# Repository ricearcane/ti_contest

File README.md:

ti_contest
==========

Files for the 2014 TI Analog Design Competition

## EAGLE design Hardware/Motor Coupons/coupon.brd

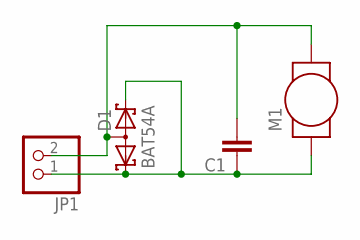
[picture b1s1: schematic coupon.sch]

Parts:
C1: C-EUC0805; C0805
D1: BAT54A; SOT23
JP1: PINHD-1X2; 1X02
M1: PAGER-PANCAKE; PANCAKE

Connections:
GND: C1.1, D1.1 (K1), D1.2 (K2), JP1.1, M1.P$1
unnamed: C1.2, D1.3 (AA), JP1.2, M1.P$2

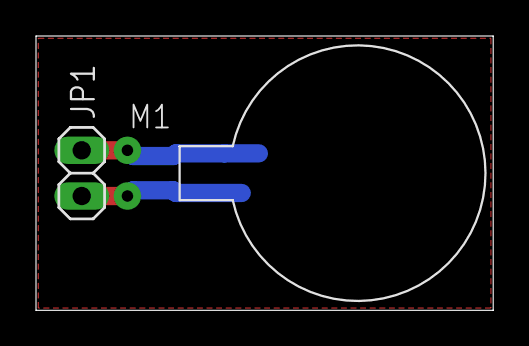
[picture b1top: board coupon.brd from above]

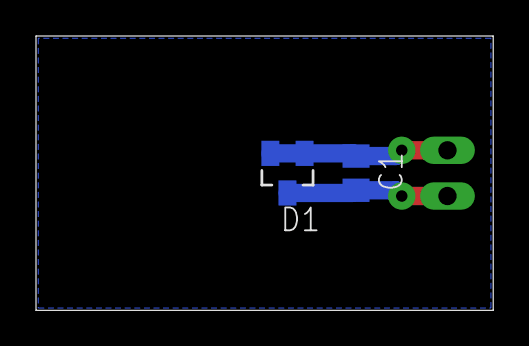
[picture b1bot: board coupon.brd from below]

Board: 2 copper layers, 25.4 x 15.2 mm, 4 parts (2 on the bottom side), 2 nets.

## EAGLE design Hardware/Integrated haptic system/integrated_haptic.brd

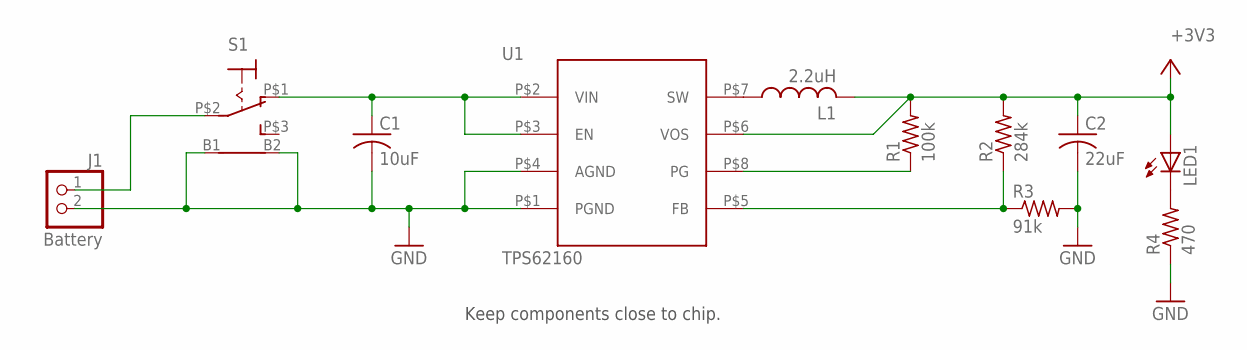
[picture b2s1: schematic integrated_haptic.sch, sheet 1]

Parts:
C1: 10uF; C1206K
C2: 22uF; C1206K
J1: Battery; 1X02
L1: 2.2uH; L2520P
LED1: LEDCHIP-LED0805; CHIP-LED0805
R1: 100k; R0603
R2: 284k; R0603
R3: 91k; R0603
R4: 470; R0603
S1: 7101MD9AQE; 7101MD9A
U1: TPS62160; VSSOP

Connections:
+3V3: C2.1, L1.2, LED1.A, R1.2, R2.2, U1.P$6 (VOS); also elsewhere on the board
GND: C1.2, C2.2, J1.2, R3.2, R4.1, S1.B1 (B), S1.B2 (B1), U1.P$1 (PGND), U1.P$4 (AGND); also elsewhere on the board
unnamed: L1.1, U1.P$7 (SW)
unnamed: J1.1, S1.P$2
unnamed: LED1.C, R4.2
unnamed: R2.1, R3.1, U1.P$5 (FB)
POWER_PG: R1.1, U1.P$8 (PG)
VBAT: C1.1, S1.P$1 (O), U1.P$2 (VIN), U1.P$3 (EN)

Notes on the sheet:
Keep components close to chip.

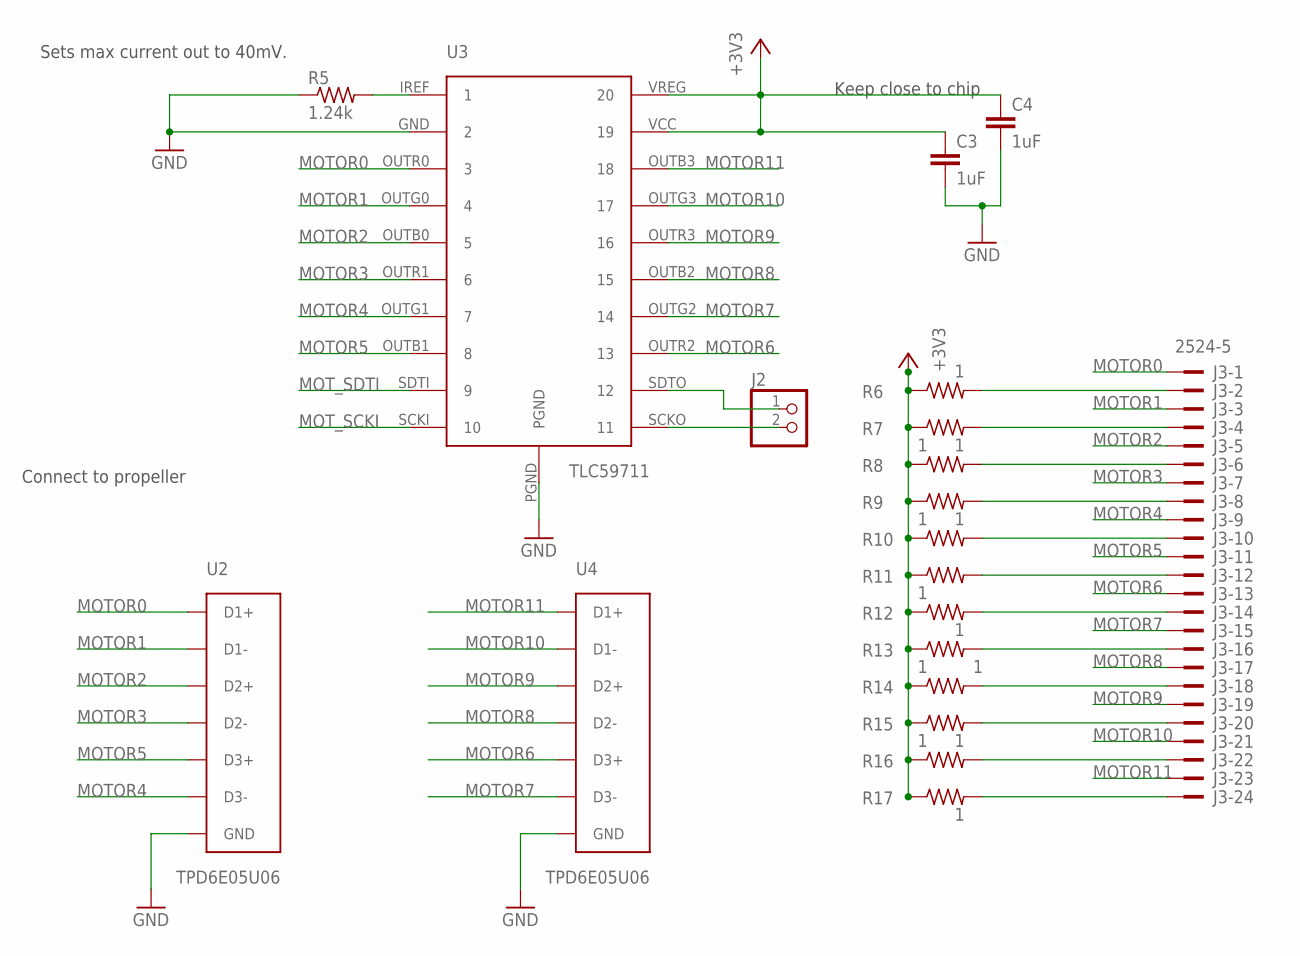
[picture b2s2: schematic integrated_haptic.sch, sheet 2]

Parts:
C3, C4: 1uF; C0805K
J2: PINHD-1X2; 1X02
J3: 2524-5; PAK100/2500-5-24
R5: 1.24k; R0603
R6, R7, R8, R9, R10, R11, R12, R13, R14, R15, R16, R17: 1; R0805
U2, U4: TPD6E05U06; PUQFN-N14
U3: TLC59711

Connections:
+3V3: C3.1, C4.1, R6.1, R7.1, R8.1, R9.1, R10.1, R11.1, R12.1, R13.1, R14.1, R15.1, R16.1, R17.1, U3.VCC (19), U3.VREG (20); also elsewhere on the board
GND: C3.2, C4.2, R5.1, U2.P$5 (GND), U2.P$10 (GND), U3.GND (2), U3.PGND, U4.P$5 (GND), U4.P$10 (GND); also elsewhere on the board
MOTOR0: J3.1, U2.P$1 (D1+), U2.P$14 (D1+), U3.OUTR0 (3)
MOTOR1: J3.3, U2.P$2 (D1-), U2.P$13 (D1-), U3.OUTG0 (4)
MOTOR2: J3.5, U2.P$3 (D2+), U2.P$12 (D2+), U3.OUTB0 (5)
MOTOR3: J3.7, U2.P$4 (D2-), U2.P$11 (D2-), U3.OUTR1 (6)
MOTOR4: J3.9, U2.P$6 (D3-), U2.P$9 (D3-), U3.OUTG1 (7)
MOTOR5: J3.11, U2.P$7 (D3+), U2.P$8 (D3+), U3.OUTB1 (8)
MOTOR6: J3.13, U3.OUTR2 (13), U4.P$7 (D3+), U4.P$8 (D3+)
MOTOR7: J3.15, U3.OUTG2 (14), U4.P$6 (D3-), U4.P$9 (D3-)
MOTOR8: J3.17, U3.OUTB2 (15), U4.P$4 (D2-), U4.P$11 (D2-)
MOTOR9: J3.19, U3.OUTR3 (16), U4.P$3 (D2+), U4.P$12 (D2+)
MOTOR10: J3.21, U3.OUTG3 (17), U4.P$2 (D1-), U4.P$13 (D1-)
MOTOR11: J3.23, U3.OUTB3 (18), U4.P$1 (D1+), U4.P$14 (D1+)
MOT_SCKI: U3.SCKI (10); also elsewhere on the board
MOT_SDTI: U3.SDTI (9); also elsewhere on the board
unnamed: R5.2, U3.IREF (1)
unnamed: J3.24, R17.2
unnamed: J3.22, R16.2
unnamed: J3.20, R15.2
unnamed: J3.18, R14.2
unnamed: J3.16, R13.2
unnamed: J3.14, R12.2
unnamed: J3.12, R11.2
unnamed: J3.10, R10.2
unnamed: J3.8, R9.2
unnamed: J3.6, R8.2
unnamed: J3.4, R7.2
unnamed: J3.2, R6.2
unnamed: J2.2, U3.SCKO (11)
unnamed: J2.1, U3.SDTO (12)

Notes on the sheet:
Sets max current out to 40mV.
Keep close to chip
Connect to propeller

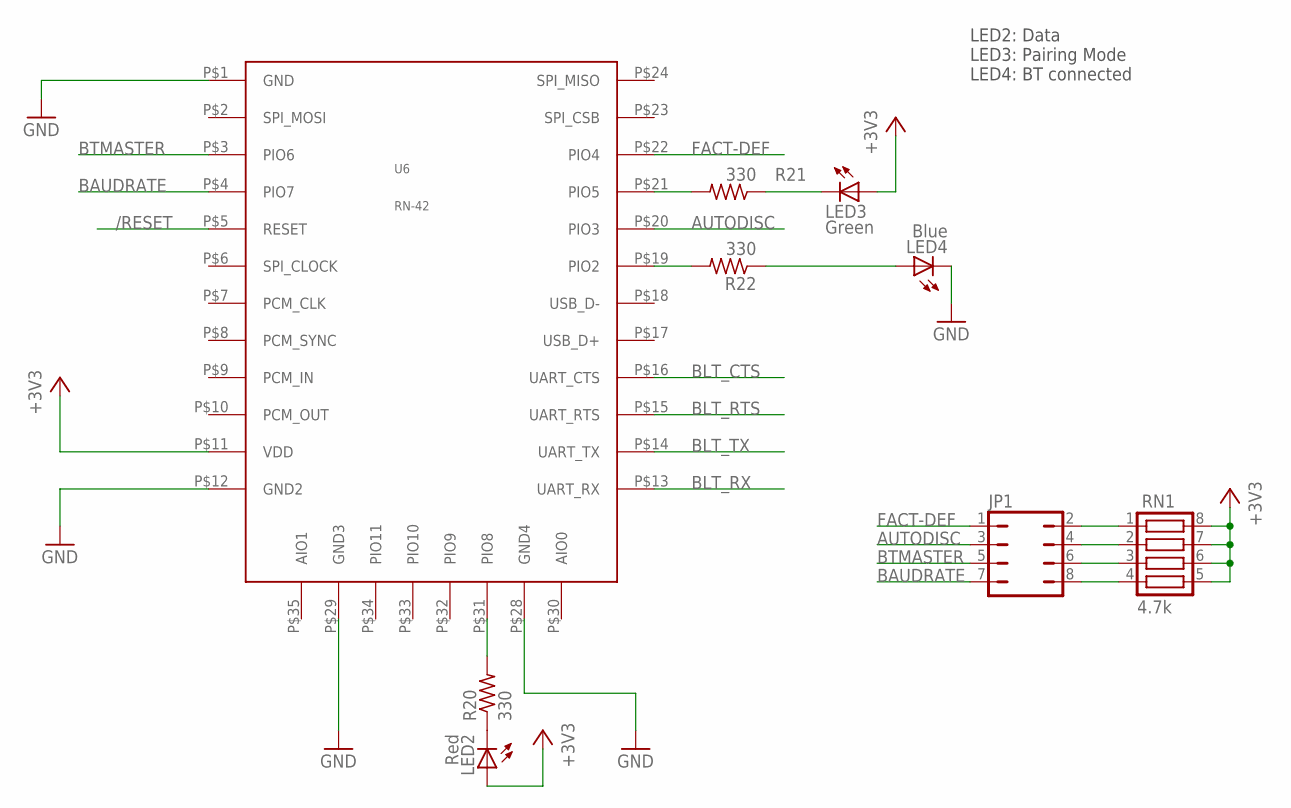
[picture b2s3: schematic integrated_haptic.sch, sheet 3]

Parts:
JP1: JP4Q
LED2: Red; CHIP-LED0805
LED3: Green; CHIP-LED0805
LED4: Blue; CHIP-LED0805
R20, R21, R22: 330; R0603
RN1: 4.7k; CTS742C083
U6: RN-42

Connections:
+3V3: LED2.A, LED3.A, RN1.5, RN1.6, RN1.7, RN1.8, U6.P$11 (VDD); also elsewhere on the board
/RESET: U6.P$5 (RESET); also elsewhere on the board
AUTODISC: JP1.3, U6.P$20 (PIO3)
BAUDRATE: JP1.7, U6.P$4 (PIO7)
BLT_CTS: U6.P$16 (UART_CTS); also elsewhere on the board
BLT_RTS: U6.P$15 (UART_RTS); also elsewhere on the board
BLT_RX: U6.P$13 (UART_RX); also elsewhere on the board
BLT_TX: U6.P$14 (UART_TX); also elsewhere on the board
BTMASTER: JP1.5, U6.P$3 (PIO6)
FACT-DEF: JP1.1, U6.P$22 (PIO4)
GND: LED4.C, U6.P$1 (GND), U6.P$12 (GND2), U6.P$28 (GND4), U6.P$29 (GND3); also elsewhere on the board
unnamed: LED2.C, R20.1
unnamed: R21.2, U6.P$21 (PIO5)
unnamed: LED3.C, R21.1
unnamed: R22.2, U6.P$19 (PIO2)
unnamed: LED4.A, R22.1
unnamed: R20.2, U6.P$31 (PIO8)
unnamed: JP1.8, RN1.4
unnamed: JP1.6, RN1.3
unnamed: JP1.4, RN1.2
unnamed: JP1.2, RN1.1

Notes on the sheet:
LED2: Data LED3: Pairing Mode LED4: BT connected

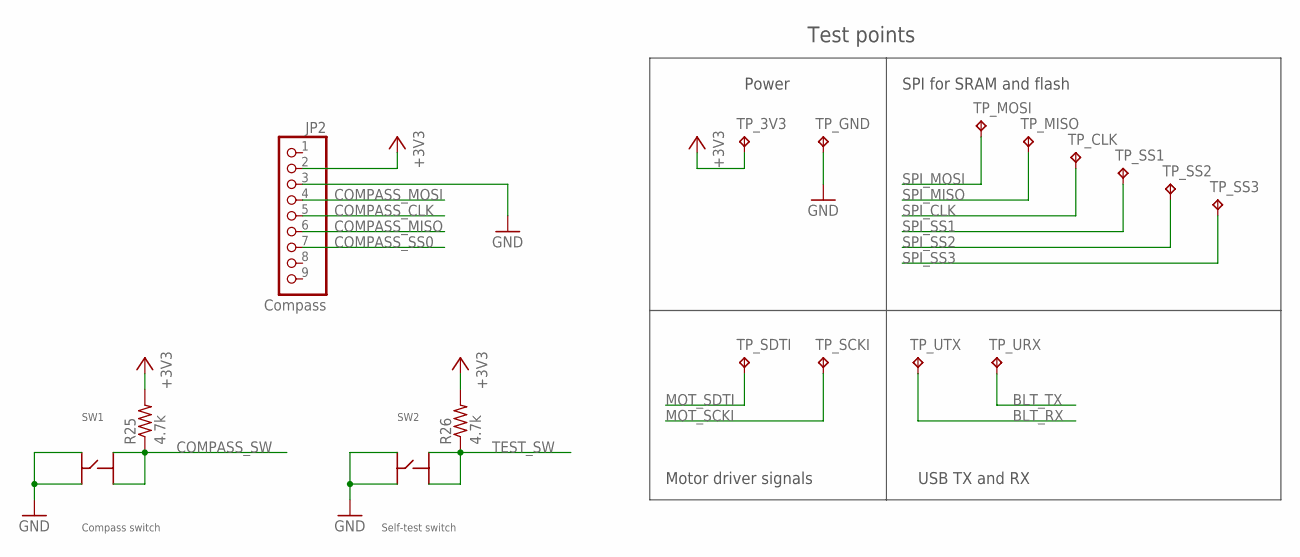
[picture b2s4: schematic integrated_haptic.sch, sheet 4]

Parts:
JP2: Compass; 1X09
R25, R26: 4.7k; R0603
SW1: Compass switch; 6MMX6MM
SW2: Self-test switch; 6MMX6MM
TP_3V3: TPPAD1-13; P1-13
TP_CLK: TPPAD1-13; P1-13
TP_GND: TPPAD1-13; P1-13
TP_MISO: TPPAD1-13; P1-13
TP_MOSI: SPI_MOSI; P1-13
TP_SCKI: TPPAD1-13; P1-13
TP_SDTI: TPPAD1-13; P1-13
TP_SS1, TP_SS2, TP_SS3: TPPAD1-13; P1-13
TP_URX: TPPAD1-13; P1-13
TP_UTX: TPPAD1-13; P1-13

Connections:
+3V3: JP2.2, R25.2, R26.2, TP_3V3.TP; also elsewhere on the board
BLT_RX: TP_UTX.TP; also elsewhere on the board
BLT_TX: TP_URX.TP; also elsewhere on the board
COMPASS_CLK: JP2.5; also elsewhere on the board
COMPASS_MISO: JP2.6; also elsewhere on the board
COMPASS_MOSI: JP2.4; also elsewhere on the board
COMPASS_SS0: JP2.7; also elsewhere on the board
COMPASS_SW: R25.1, SW1.P$2, SW1.P$4; also elsewhere on the board
GND: JP2.3, SW1.P$1, SW1.P$3, SW2.P$1, SW2.P$3, TP_GND.TP; also elsewhere on the board
MOT_SCKI: TP_SCKI.TP; also elsewhere on the board
MOT_SDTI: TP_SDTI.TP; also elsewhere on the board
SPI_CLK: TP_CLK.TP; also elsewhere on the board
SPI_MISO: TP_MISO.TP; also elsewhere on the board
SPI_MOSI: TP_MOSI.TP; also elsewhere on the board
SPI_SS1: TP_SS1.TP; also elsewhere on the board
SPI_SS2: TP_SS2.TP; also elsewhere on the board
SPI_SS3: TP_SS3.TP; also elsewhere on the board
TEST_SW: R26.1, SW2.P$2, SW2.P$4; also elsewhere on the board

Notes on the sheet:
Power
SPI for SRAM and flash
Motor driver signals
USB TX and RX
Test points

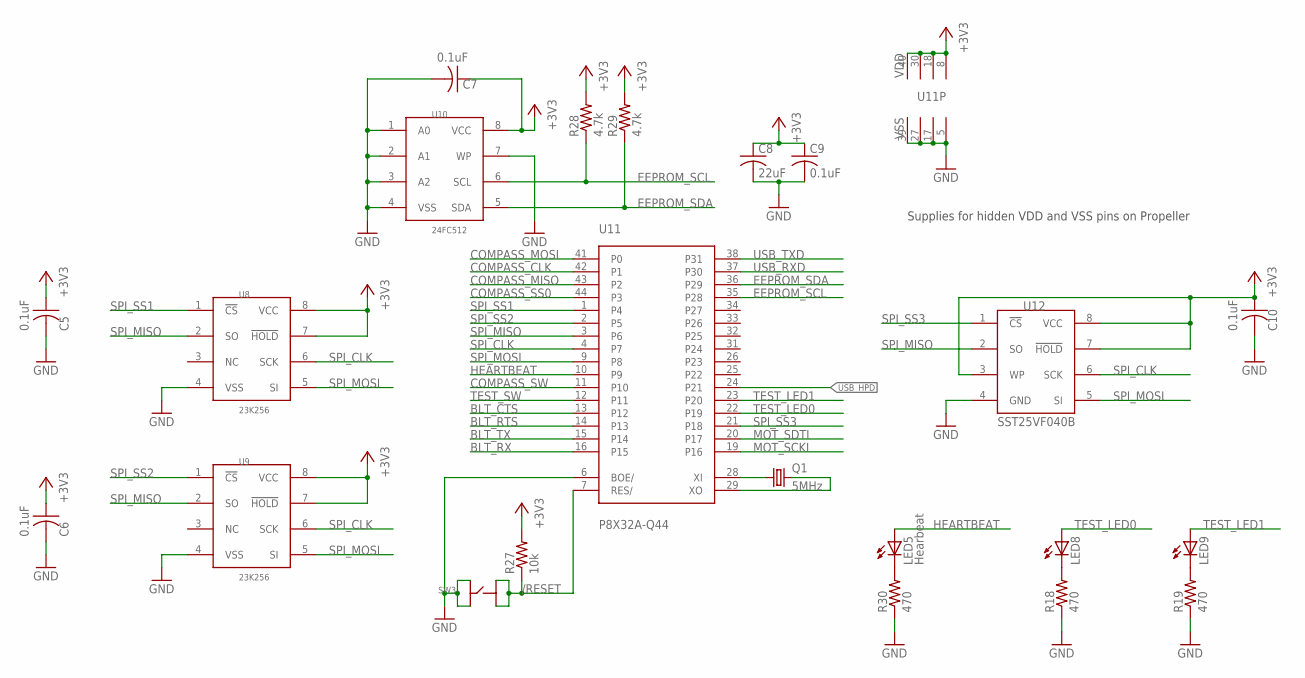
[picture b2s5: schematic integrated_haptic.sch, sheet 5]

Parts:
C5, C6, C7, C9, C10: 0.1uF; C0805K
C8: 22uF; C1206K
LED5: Hearbeat; CHIP-LED0805
LED8, LED9: LEDCHIP-LED0805; CHIP-LED0805
Q1: 5MHz; HC49UP
R18, R19, R30: 470; R0603
R27: 10k; R0603
R28, R29: 4.7k; R0603
SW3: PUSHBUTTON; 6MMX6MM
U8, U9: 23K256; SOIC8
U10: 24FC512; SOIC8
U11: P8X32A-Q44
U12: SST25VF040B; SOIC8

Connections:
+3V3: C5.1, C6.1, C7.1, C8.1, C9.1, C10.1, R27.2, R28.2, R29.2, U8.7 (!HOLD), U8.8 (VCC), U9.7 (!HOLD), U9.8 (VCC), U10.8 (VCC), U11.8 (VDD), U11.18 (VDD), U11.30 (VDD), U11.40 (VDD), U12.3 (WP), U12.7 (!HOLD), U12.8 (VCC); also elsewhere on the board
/RESET: R27.1, SW3.P$2, SW3.P$4, U11.7 (RES/); also elsewhere on the board
BLT_CTS: U11.13 (P12); also elsewhere on the board
BLT_RTS: U11.14 (P13); also elsewhere on the board
BLT_RX: U11.16 (P15); also elsewhere on the board
BLT_TX: U11.15 (P14); also elsewhere on the board
COMPASS_CLK: U11.42 (P1); also elsewhere on the board
COMPASS_MISO: U11.43 (P2); also elsewhere on the board
COMPASS_MOSI: U11.41 (P0); also elsewhere on the board
COMPASS_SS0: U11.44 (P3); also elsewhere on the board
COMPASS_SW: U11.11 (P10); also elsewhere on the board
EEPROM_SCL: R28.1, U10.6 (SCL), U11.35 (P28)
EEPROM_SDA: R29.1, U10.5 (SDA), U11.36 (P29)
GND: C5.2, C6.2, C7.2, C8.2, C9.2, C10.2, R18.1, R19.1, R30.1, SW3.P$1, SW3.P$3, U8.4 (VSS), U9.4 (VSS), U10.1 (A0), U10.2 (A1), U10.3 (A2), U10.4 (VSS), U10.7 (WP), U11.5 (VSS), U11.6 (BOE/), U11.17 (VSS), U11.27 (VSS), U11.39 (VSS), U12.4 (GND); also elsewhere on the board
HEARTBEAT: LED5.A, U11.10 (P9)
MOT_SCKI: U11.19 (P16); also elsewhere on the board
MOT_SDTI: U11.20 (P17); also elsewhere on the board
unnamed: LED8.C, R18.2
unnamed: LED5.C, R30.2
unnamed: LED9.C, R19.2
SPI_CLK: U8.6 (SCK), U9.6 (SCK), U11.4 (P7), U12.6 (SCK); also elsewhere on the board
SPI_MISO: U8.2 (SO), U9.2 (SO), U11.3 (P6), U12.2 (SO); also elsewhere on the board
SPI_MOSI: U8.5 (SI), U9.5 (SI), U11.9 (P8), U12.5 (SI); also elsewhere on the board
SPI_SS1: U8.1 (!CS), U11.1 (P4); also elsewhere on the board
SPI_SS2: U9.1 (!CS), U11.2 (P5); also elsewhere on the board
SPI_SS3: U11.21 (P18), U12.1 (!CS); also elsewhere on the board
TEST_LED0: LED8.A, U11.22 (P19)
TEST_LED1: LED9.A, U11.23 (P20)
TEST_SW: U11.12 (P11); also elsewhere on the board
USB_HPD: U11.24 (P21); also elsewhere on the board
USB_RXD: U11.37 (P30); also elsewhere on the board
USB_TXD: U11.38 (P31); also elsewhere on the board
XTAL0: Q1.2, U11.29 (XO)
XTAL1: Q1.1, U11.28 (XI)

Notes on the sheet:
Supplies for hidden VDD and VSS pins on Propeller

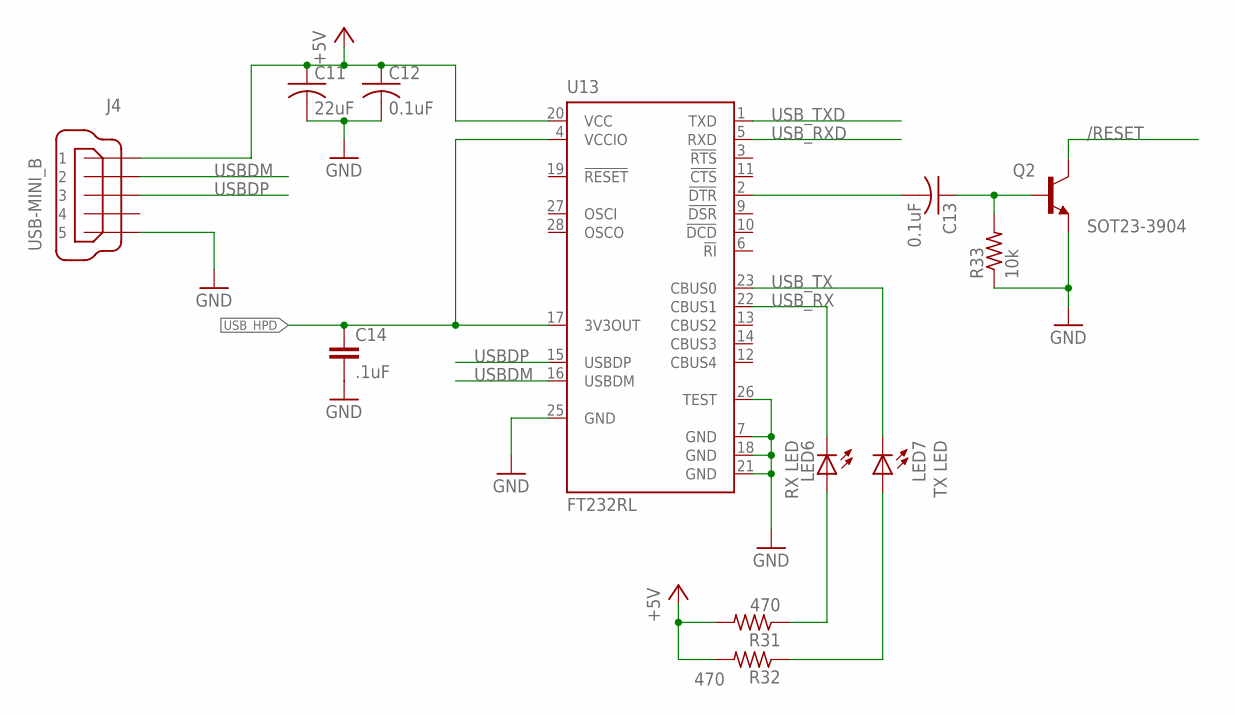
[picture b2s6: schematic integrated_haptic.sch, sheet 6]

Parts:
C11: 22uF; C1206K
C12, C13: 0.1uF; C0805K
C14: .1uF; C0805
J4: USB-MINI_B; USB_MINI_B
LED6: RX LED; CHIP-LED0805
LED7: TX LED; CHIP-LED0805
Q2: SOT23-3904; SOT23-BEC
R31, R32: 470; R0603
R33: 10k; R0603
U13: FT232RL; SSOP28

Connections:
+5V: C11.1, C12.1, J4.1, R31.2, R32.2, U13.20 (VCC)
/RESET: Q2.C; also elsewhere on the board
GND: C11.2, C12.2, C14.2, J4.5, Q2.E, R33.1, U13.7 (GND), U13.18 (GND), U13.21 (GND), U13.25 (GND), U13.26 (TEST); also elsewhere on the board
unnamed: C13.2, U13.2 (!DTR)
unnamed: LED6.A, R31.1
unnamed: LED7.A, R32.1
unnamed: C13.1, Q2.B, R33.2
USBDM: J4.2, U13.16 (USBDM)
USBDP: J4.3, U13.15 (USBDP)
USB_HPD: C14.1, U13.4 (VCCIO), U13.17 (3V3OUT); also elsewhere on the board
USB_RX: LED6.C, U13.22 (CBUS1)
USB_RXD: U13.5 (RXD); also elsewhere on the board
USB_TX: LED7.C, U13.23 (CBUS0)
USB_TXD: U13.1 (TXD); also elsewhere on the board

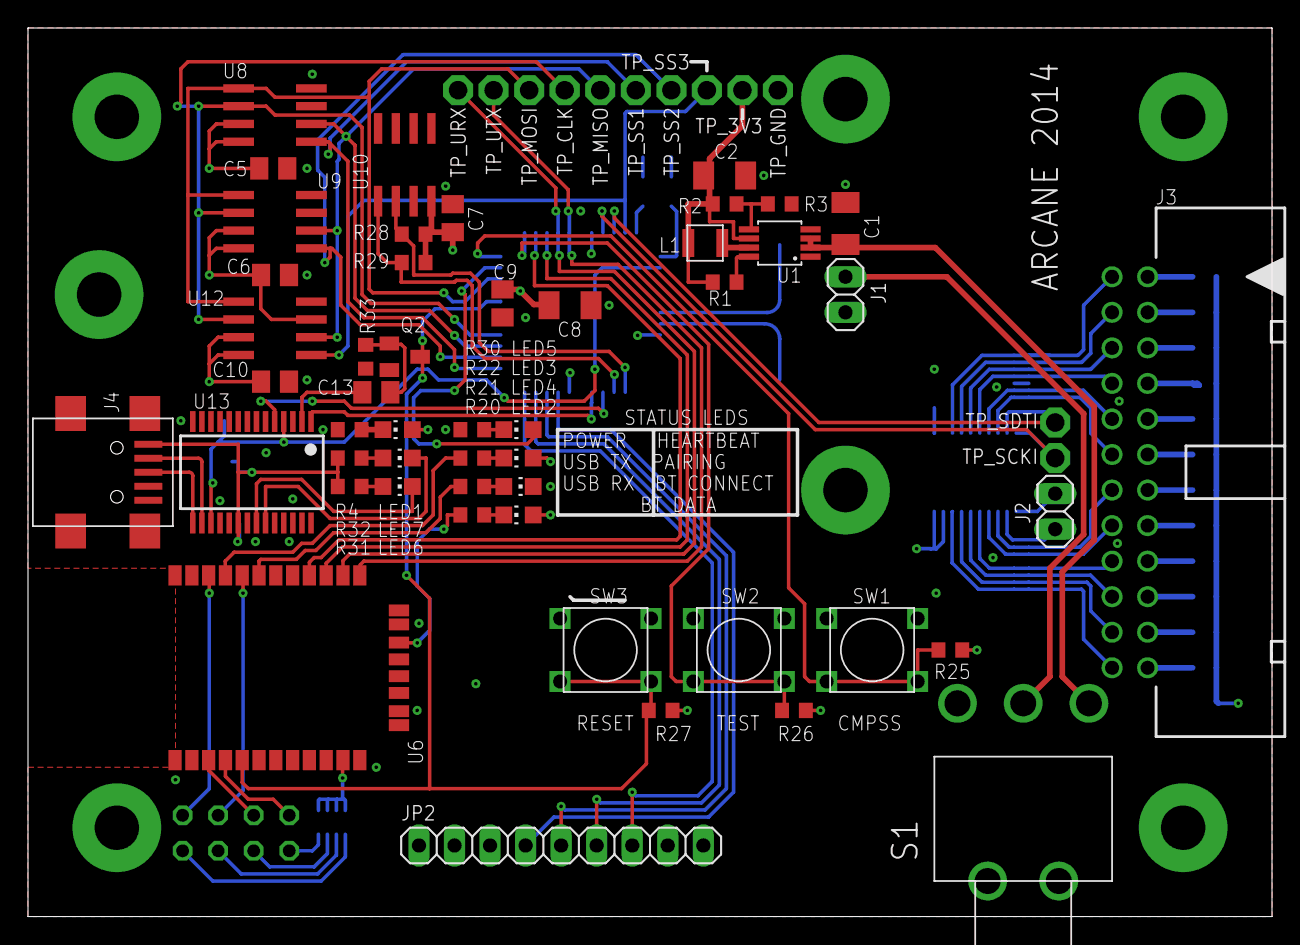
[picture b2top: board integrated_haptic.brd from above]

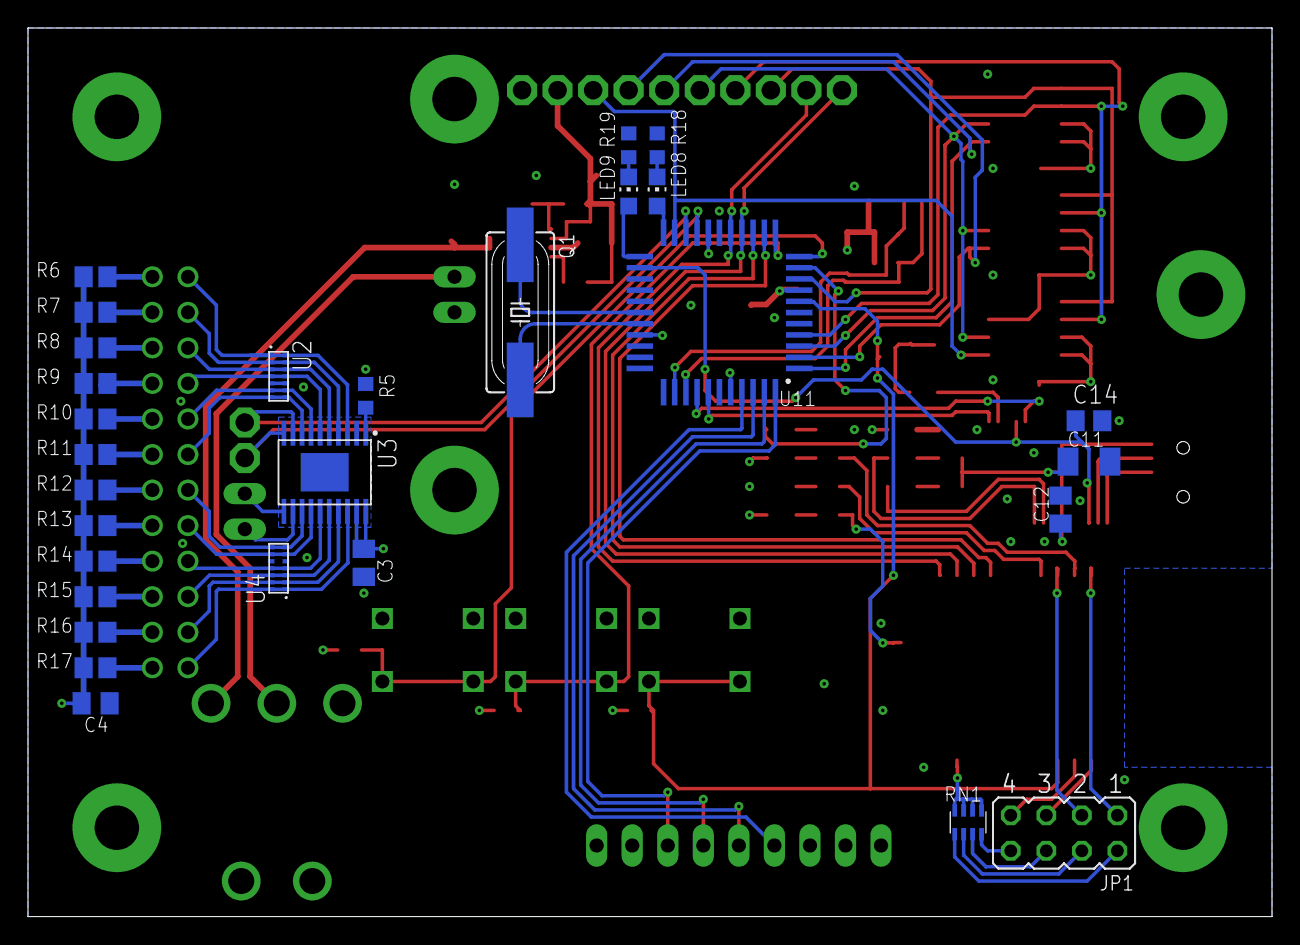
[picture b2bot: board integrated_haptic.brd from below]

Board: 4 copper layers, 88.9 x 63.5 mm, 91 parts (29 on the bottom side), 90 nets.

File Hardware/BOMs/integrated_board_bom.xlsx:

Value | Device | Package | Parts | Description | Qty | Digikey Part Number | Customer Reference | Notes
1 | R-US_R0805 | R0805 | R6, R7, R8, R9, R10, R11, R12, R13, R14, R15, R16, R17 | RESISTOR, American symbol | 12 | RMCF0805JT1R00CT-ND | R6, R7, R8, R9, R10, R11, R12, R13, R14, R15, R16, R17
330 | R-US_R0603 | R0603 | R20, R21, R22 | RESISTOR, American symbol | 3 | 1276-5050-1-ND | R20, R21, R22
470 | R-US_R0603 | R0603 | R4, R18, R19, R30, R31, R32 | RESISTOR, American symbol | 6 | 311-470GRCT-ND | R4, R18, R19, R30, R31, R32
1.24k | R-US_R0603 | R0603 | R5 | RESISTOR, American symbol | 1 | P1.24KHCT-ND | R5
4.7k | R-US_R0603 | R0603 | R25, R26, R28, R29 | RESISTOR, American symbol | 4 | 311-4.7KGRCT-ND | R25, R26, R28, R29
10k | R-US_R0603 | R0603 | R27, R33 | RESISTOR, American symbol | 2 | 311-10KGRCT-ND | R27, R33
91k | R-US_R0603 | R0603 | R3 | RESISTOR, American symbol | 1 | 311-91.0KHRCT-ND | R3
100k | R-US_R0603 | R0603 | R1 | RESISTOR, American symbol | 1 | 311-100KGRCT-ND | R1
284k | R-US_R0603 | R0603 | R2 | RESISTOR, American symbol | 1 | RR08P284KDCT-ND | R2
4.7k | CTS742C083 | CTS742C083 | RN1 | Chip Resistor Array 4 Single Resistor | 1 | TC164J-4.7KCT-ND | RN1
0.1uF | C-USC0805K | C0805K | C5, C6, C7, C9, C10, C12, C13 | CAPACITOR, American symbol | 7 | 311-1361-1-ND | C5, C6, C7, C9, C10, C12, C13
1uF | C-EUC0805K | C0805K | C3, C4 | CAPACITOR, European symbol | 2 | 1276-1029-1-ND | C3, C4
10uF | C-USC1206K | C1206K | C1 | CAPACITOR, American symbol | 1 | 587-1353-1-ND | C1
22uF | C-USC1206K | C1206K | C2, C8, C11 | CAPACITOR, American symbol | 3 | 1276-3048-1-ND | C2, C8, C11
2.2uH | L-USL2520P | L2520P | L1 | INDUCTOR, American symbol | 1 | 445-3670-1-ND | L1
Amber | LEDCHIP-LED0805 | CHIP-LED0805 | LED8 | LED | 1 | 516-1431-1-ND | LED8
Blue | LEDCHIP-LED0805 | CHIP-LED0805 | LED4 | LED | 1 | 160-1645-1-ND | LED4
Green | LEDCHIP-LED0805 | CHIP-LED0805 | LED3,LED7 | LED | 2 | 160-1423-1-ND | LED3,LED7
Red | LEDCHIP-LED0805 | CHIP-LED0805 | LED1, LED2, LED6, LED9 | LED | 4 | 160-1415-1-ND | LED1, LED2, LED6, LED9
White | LEDCHIP-LED0805 | CHIP-LED0805 | LED5 | LED | 1 | 160-1738-1-ND | LED5
23K256 | 23K256 | SOIC8 | U8, U9 |  | 2 | 23K256-I/SN-ND | U8, U9
24FC512 | 24FC512 | SOIC8 | U10 |  | 1 | 24FC512-I/SN-ND | U10
FT232RL | FT232RL | SSOP28 | U13 |  | 1 | 768-1007-1-ND | U13
P8X32A-Q44 | Propeller | P8X32A-Q44 | U11 |  | 1 | P8X32A-Q44-ND | U11
RN-42 | Bluetooth Module | RN-42 | U6 |  | 1 | 740-1038-ND | U6
SST25VF040B | SST25VF040B | SOIC8 | U12 |  | 1 | 804-25VF040B5CSAF | U12 | MOUSER PART
TLC59711 | TLC59711 | TLC59711 | U3 |  | 1 | 296-36745-1-ND | U3
TPD6E05U06 | TPD6E05U06 | PUQFN-N14 | U2, U4 | TPD6E05U06 6-channel ESD Protection device | 2 | N/A | U2, U4 | New product - need to sample from TI
TPS62160 | TPS62160 | VSSOP | U1 |  | 1 | 296-30318-1-ND | U1
2524-5 | 2524-5 | PAK100/2500-5-24 | J3 | 3M (TM) Pak 100 4-Wall Header | 1 | MHE24K-ND | J3
1X02 Header Male | PINHD-1X2 | 1X02 | J1, J2 | PIN HEADER | 2 |  | J1, J2
1X09 Header | PINHD-1X9 | 1X09 | JP2 | PIN HEADER | 1 |  | JP2
 | JP4Q | JP4Q | JP1 | JUMPER | 4 | 3M9580-ND | JP1
 | PUSHBUTTON | 6MMX6MM | SW1, SW2, SW3 |  | 3 | 450-1804-ND | SW1, SW2, SW3
 | 7101MD9AQE | 7101MD9A | S1 | TOGGLE SWITCH | 1 | CKN1047-ND | S1
5MHz | CRYSTALHC49UP | HC49UP | Q1 | CRYSTAL | 1 | XC1264CT-ND | Q1
SOT23-3904 | MMBT918LT1-NPN-SOT23-BEC | SOT23-BEC | Q2 | NPN Transistror | 1 | MMBT918LT1GOSCT-ND | Q2
USB-MINI_B | USB-MINI_B | USB_MINI_B | J4 | MINI USB-B Conector | 1 | H2959CT-ND | J4

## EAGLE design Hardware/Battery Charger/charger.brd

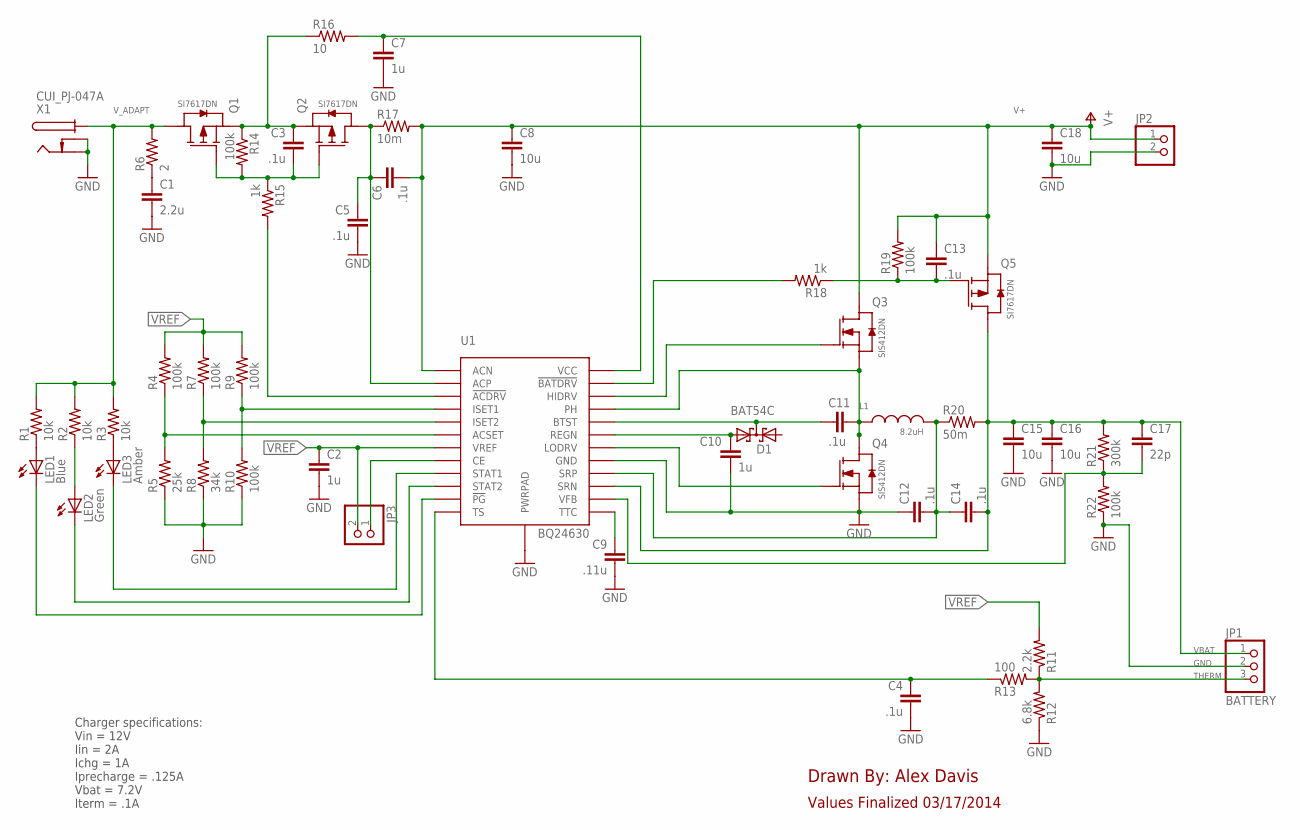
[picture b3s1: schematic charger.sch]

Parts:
C1: 2.2u; C0603
C2, C7, C10: 1u; C0603
C3, C4, C5, C6, C11, C12, C13, C14: .1u; C0603
C8, C15, C16, C18: 10u; C0805
C9: .11u; C0603
C17: 22p; C0603
D1: BAT54C; SOT23
JP1: BATTERY; 1X03
JP2, JP3: PINHD-1X2; 1X02
L1: 8.2uH; IHLP-2525CZ
LED1: Blue; CHIPLED_0805
LED2: Green; CHIPLED_0805
LED3: Amber; CHIPLED_0805
Q1, Q2, Q5: SI7617DN; POWERPAK1212-8
Q3, Q4: SIS412DN; POWERPAK1212-8
R1, R2, R3: 10k; R0603
R4, R7, R9, R10, R14, R19, R22: 100k; R0603
R5: 25k; R0603
R6: 2; R2512
R8: 34k; R0603
R11: 2.2k; R0603
R12: 6.8k; R0603
R13: 100; R0603
R15, R18: 1k; R0603
R16: 10; R1206
R17: 10m; R2010
R20: 50m; R2010
R21: 300k; R0603
U1: BQ24630; PVQFN-24
X1: CUI_PJ-047A; PJ-047A

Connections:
!PG: LED1.C, U1.P$8 (!PG)
GND: C1.2, C2.2, C4.2, C5.2, C7.2, C8.2, C9.2, C10.2, C12.1, C15.2, C16.2, C18.2, JP1.2, JP2.2, Q4.P$1 (S), Q4.P$2 (S), Q4.P$3 (S), R5.1, R8.1, R10.1, R12.1, R22.1, U1.P$17 (GND), U1.P$25 (PWRPAD), X1.2, X1.3
unnamed: C3.1, Q1.P$1 (S), Q1.P$2 (S), Q1.P$3 (S), Q2.P$1 (S), Q2.P$2 (S), Q2.P$3 (S), R14.1, R16.1
unnamed: C3.2, Q1.P$4 (G), Q2.P$4 (G), R14.2, R15.1
unnamed: C10.1, D1.2 (A2), U1.P$18 (REGN)
unnamed: C5.1, C6.1, Q2.P$5 (D), Q2.P$6 (D), Q2.P$7 (D), Q2.P$8 (D), Q2.P$9 (D), R17.1, U1.P$2 (ACP)
unnamed: C12.2, C14.1, L1.P$2, R20.1, U1.P$14 (SRP)
unnamed: JP3.1, U1.P$4 (CE)
unnamed: C11.1, D1.3 (CC), U1.P$22 (BTST)
unnamed: Q4.P$4 (G), U1.P$19 (LODRV)
unnamed: Q3.P$4 (G), U1.P$21 (HIDRV)
unnamed: C11.2, L1.P$1, Q3.P$1 (S), Q3.P$2 (S), Q3.P$3 (S), Q4.P$5 (D), Q4.P$6 (D), Q4.P$7 (D), Q4.P$8 (D), Q4.P$9 (D), U1.P$20 (PH)
unnamed: C1.1, R6.1
unnamed: R4.1, R5.2, U1.P$16 (ACSET)
unnamed: R15.2, U1.P$3 (!ACDRV)
unnamed: R7.1, R8.2, U1.P$15 (ISET2)
unnamed: R9.1, R10.2, U1.P$11 (ISET1)
unnamed: LED1.A, R1.1
unnamed: LED2.A, R2.1
unnamed: LED3.A, R3.1
unnamed: C4.1, R13.1, U1.P$6 (TS)
unnamed: C9.1, U1.P$7 (TTC)
unnamed: C17.2, R21.1, R22.2, U1.P$12 (VFB)
unnamed: R18.2, U1.P$23 (!BATDRV)
unnamed: C13.2, Q5.P$4 (G), R18.1, R19.1
STAT1: LED3.C, U1.P$5 (STAT1)
STAT2: LED2.C, U1.P$9 (STAT2)
THERM: JP1.3, R11.1, R12.2, R13.2
V+: C6.2, C8.1, C13.1, C18.1, JP2.1, Q3.P$5 (D), Q3.P$6 (D), Q3.P$7 (D), Q3.P$8 (D), Q3.P$9 (D), Q5.P$1 (S), Q5.P$2 (S), Q5.P$3 (S), R17.2, R19.2, U1.P$1 (ACN)
VBAT: C14.2, C15.1, C16.1, C17.1, JP1.1, Q5.P$5 (D), Q5.P$6 (D), Q5.P$7 (D), Q5.P$8 (D), Q5.P$9 (D), R20.2, R21.2, U1.P$13 (SRN)
VCC: C7.1, R16.2, U1.P$24 (VCC)
VREF: C2.1, JP3.2, R4.2, R7.2, R9.2, R11.2, U1.P$10 (VREF)
V_ADAPT: Q1.P$5 (D), Q1.P$6 (D), Q1.P$7 (D), Q1.P$8 (D), Q1.P$9 (D), R1.2, R2.2, R3.2, R6.2, X1.1

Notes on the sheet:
Drawn By: Alex Davis
Charger specifications: Vin = 12V Iin = 2A Ichg = 1A Iprecharge = .125A Vbat = 7.2V Iterm = .1A
Values Finalized 03/17/2014

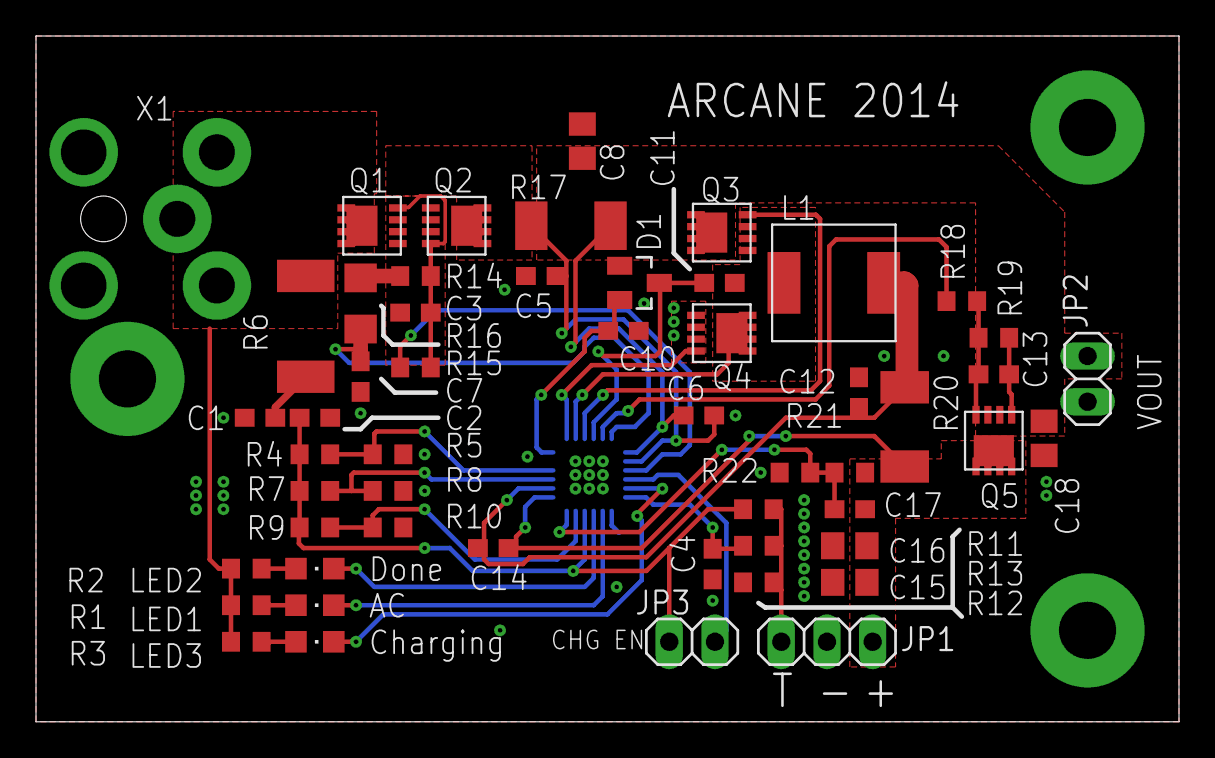
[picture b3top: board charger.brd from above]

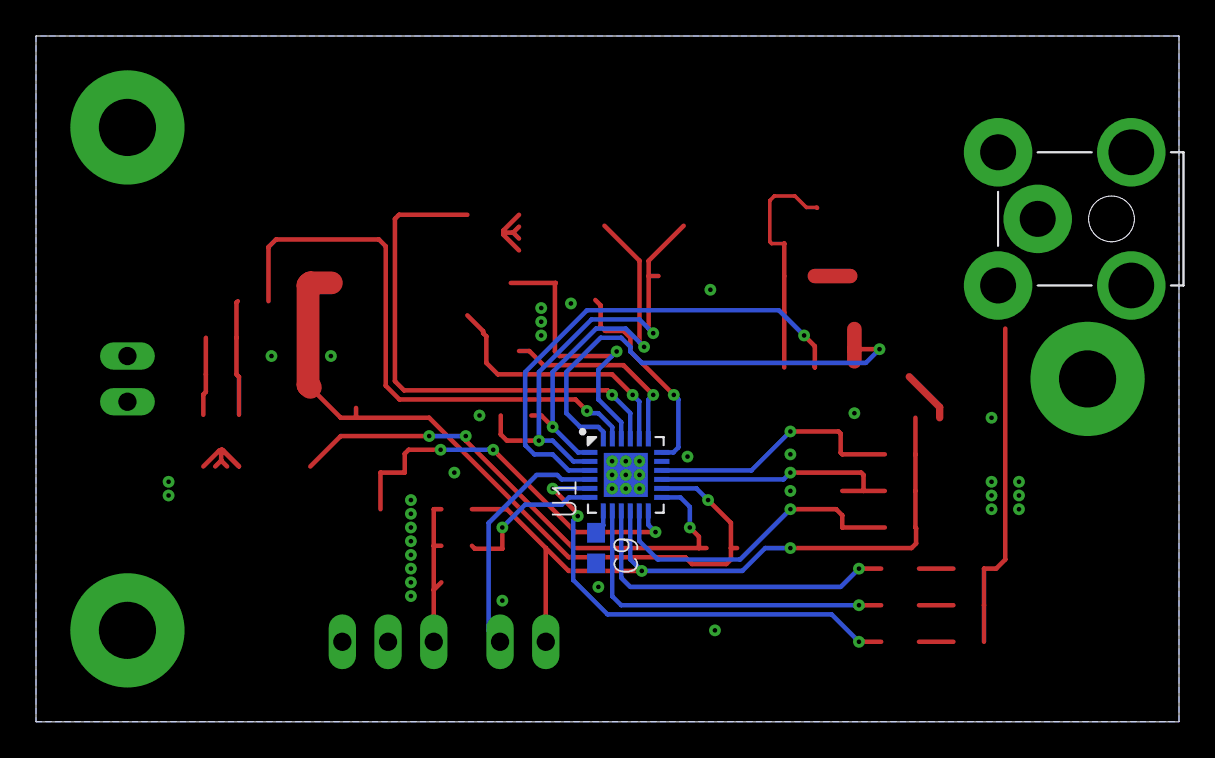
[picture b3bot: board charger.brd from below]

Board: 2 copper layers, 63.5 x 38.1 mm, 55 parts (3 on the bottom side), 33 nets.

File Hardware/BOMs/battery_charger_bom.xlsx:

Value | Device | Package | Parts | Description | Qty | Digikey Part Number | Customer Reference
10m | R-US_R2010 | R2010 | R17 | RESISTOR, American symbol | 1 | RHM.010ASCT-ND | R17
50m | R-US_R2010 | R2010 | R20 | RESISTOR, American symbol | 1 | CSRN2010FK50L0CT-ND | R20
2 | R-US_R2512 | R2512 | R6 | RESISTOR, American symbol | 1 | PT2.0YCT-ND | R6
10 | R-US_R1206 | R1206 | R16 | RESISTOR, American symbol | 1 | 311-10.0FRCT-ND | R16
100 | R-US_R0603 | R0603 | R13 | RESISTOR, American symbol | 1 | 311-100GRCT-ND | R13
1k | R-US_R0603 | R0603 | R15, R18 | RESISTOR, American symbol | 5 | 311-1.00KHRCT-ND | R15, R18 | Extras for LEDs
2.2k | R-US_R0603 | R0603 | R11 | RESISTOR, American symbol | 1 | 311-2.20KHRCT-ND | R11
6.8k | R-US_R0603 | R0603 | R12 | RESISTOR, American symbol | 1 | 311-6.80KHRCT-ND | R12
10k | R-US_R0603 | R0603 | R1, R2, R3 | RESISTOR, American symbol | 3 | 311-10KGRCT-ND | R1, R2, R3
25k | R-US_R0603 | R0603 | R5 | RESISTOR, American symbol | 1 | PNM0603-25KBCT-ND | R5
34k | R-US_R0603 | R0603 | R8 | RESISTOR, American symbol | 1 | RMCF0603FT34K0CT-ND | R8
100k | R-US_R0603 | R0603 | R4, R7, R9, R10, R14, R19, R22 | RESISTOR, American symbol | 7 | 311-100KHRCT-ND | R4, R7, R9, R10, R14, R19, R22
300k | R-US_R0603 | R0603 | R21 | RESISTOR, American symbol | 1 | P300KHCT-ND | R21
22p | C-EUC0603 | C0603 | C17 | CAPACITOR, European symbol | 1 | 445-5366-1-ND | C17
.1u | C-EUC0603 | C0603 | C3, C4, C5, C6, C9, C11, C12, C13, C14 | CAPACITOR, European symbol | 9 | 399-7844-1-ND | C3, C4, C5, C6, C9, C11, C12, C13, C14
1u | C-EUC0603 | C0603 | C2, C7, C10 | CAPACITOR, European symbol | 3 | 587-2400-1-ND | C2, C7, C10
2.2u | C-EUC0603 | C0603 | C1 | CAPACITOR, European symbol | 1 | 445-8025-1-ND | C1
10u | C-EUC0805 | C0805 | C8, C15, C16, C18 | CAPACITOR, European symbol | 4 | 445-11516-1-ND | C8, C15, C16, C18
8.2uH | IHLP-2525CZ-01 | IHLP-2525CZ | L1 |  | 1 | 541-1012-1-ND | L1
Amber | LEDCHIPLED_0805 | LEDCHIPLED_0805 | LED3 | LED | 1 | 516-1431-1-ND | LED3
Blue | LEDCHIPLED_0805 | LEDCHIPLED_0805 | LED1 | LED | 1 | 160-1645-1-ND | LED1
Green | LEDCHIPLED_0805 | CHIPLED_0805 | LED2 | LED | 1 | 160-1423-1-ND | LED2
BAT54C | BAT54C | SOT23 | D1 | Schottky Diodes | 1 | BAT54CT-ND | D1
BQ24630 | BQ24630 | PVQFN-24 | U1 |  | 1 | 296-25761-1-ND | U1
SI7617DN | SI7617DN | POWERPAK1212-8 | Q1, Q2, Q5 |  | 3 | SI7617DN-T1-GE3CT-ND | Q1, Q2, Q5
SIS412DN | SIS412DN | POWERPAK1212-8 | Q3, Q4 |  | 2 | SIS412DN-T1-GE3CT-ND | Q3, Q4
 | 733980-62 | 733980-62 | X1 | FEMALE PRINT CONNECTOR | 1 | CP-047A-ND | X1
 | PINHD-1X2 | 1X02 | JP2, JP3 | PIN HEADER | 2 |  | JP2, JP3
BATTERY | PINHD-1X3 | 1X03 | JP1 | PIN HEADER | 1 |  | JP1

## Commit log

2014-05-25 Added report and hardware files
2014-05-25 Added software
    For haptics and sensors
2014-05-25 Added pictures
2014-05-25 Added current haptic code files
    Some late compass code changes needed to be added
2014-05-25 Updated report
    Added picture of how system should be worn by user.
